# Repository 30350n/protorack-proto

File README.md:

# protorack
A collection of breadboard plugins to prototype eurorack modules

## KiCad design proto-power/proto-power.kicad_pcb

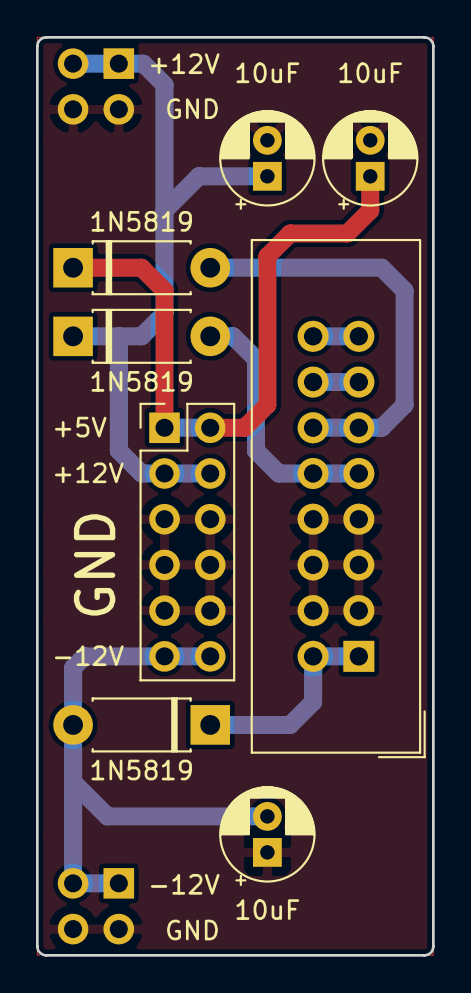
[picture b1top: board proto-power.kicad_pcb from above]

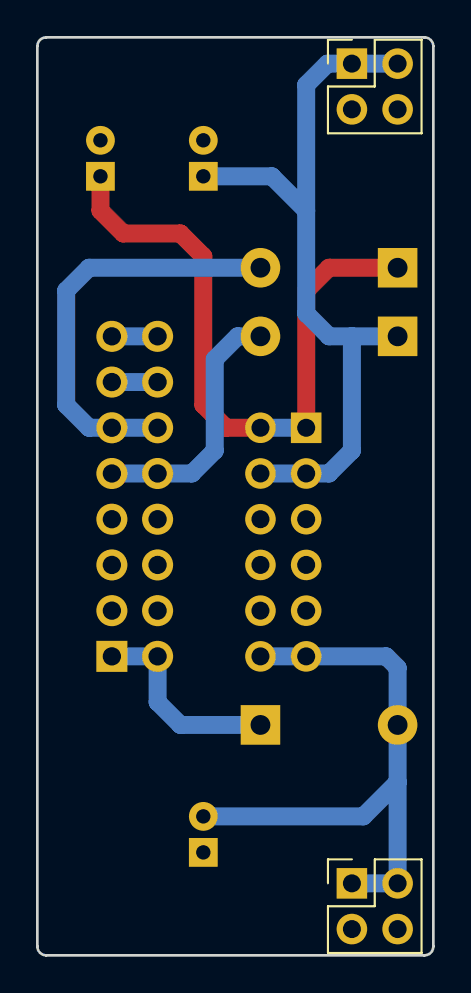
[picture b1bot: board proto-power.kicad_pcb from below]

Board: 2 copper layers, 22.0 x 51.0 mm, 10 parts (2 on the bottom side), 9 nets.

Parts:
C1, C2, C3: 10uF; CP_Radial_D5.0mm_P2.00mm_silk
D1, D2, D3: 1N5819; D_DO-41_SOD81_P7.62mm_Horizontal_silk
J1: Conn_02x08_Counter_Clockwise; IDC-Header_2x08_P2.54mm_Vertical
J2, J3: Conn_02x02_Odd_Even; PinHeader_2x02_P2.54mm_Vertical
J4: Conn_02x06_Odd_Even; PinHeader_2x06_P2.54mm_Vertical

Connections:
+5V: C1.1, D1.1, J4.1, J4.2
+12V: C2.1, D2.1, J2.1, J2.2, J4.3, J4.4
-12V: C3.2, D3.2, J3.1, J3.2, J4.11, J4.12
GND: C1.2, C2.2, C3.1, J1.3, J1.4, J1.5, J1.6, J1.7, J1.8, J2.3, J2.4, J3.3, J3.4, J4.5, J4.6, J4.7, J4.8, J4.9, J4.10
unnamed: D1.2, J1.11, J1.12
unnamed: D2.2, J1.9, J1.10
unnamed: D3.1, J1.1, J1.2
unnamed: J1.13, J1.14
unnamed: J1.15, J1.16

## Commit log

2020-10-30 Add proto-power
2020-10-30 Add template project, Remove designator from proto-power silkscreen
